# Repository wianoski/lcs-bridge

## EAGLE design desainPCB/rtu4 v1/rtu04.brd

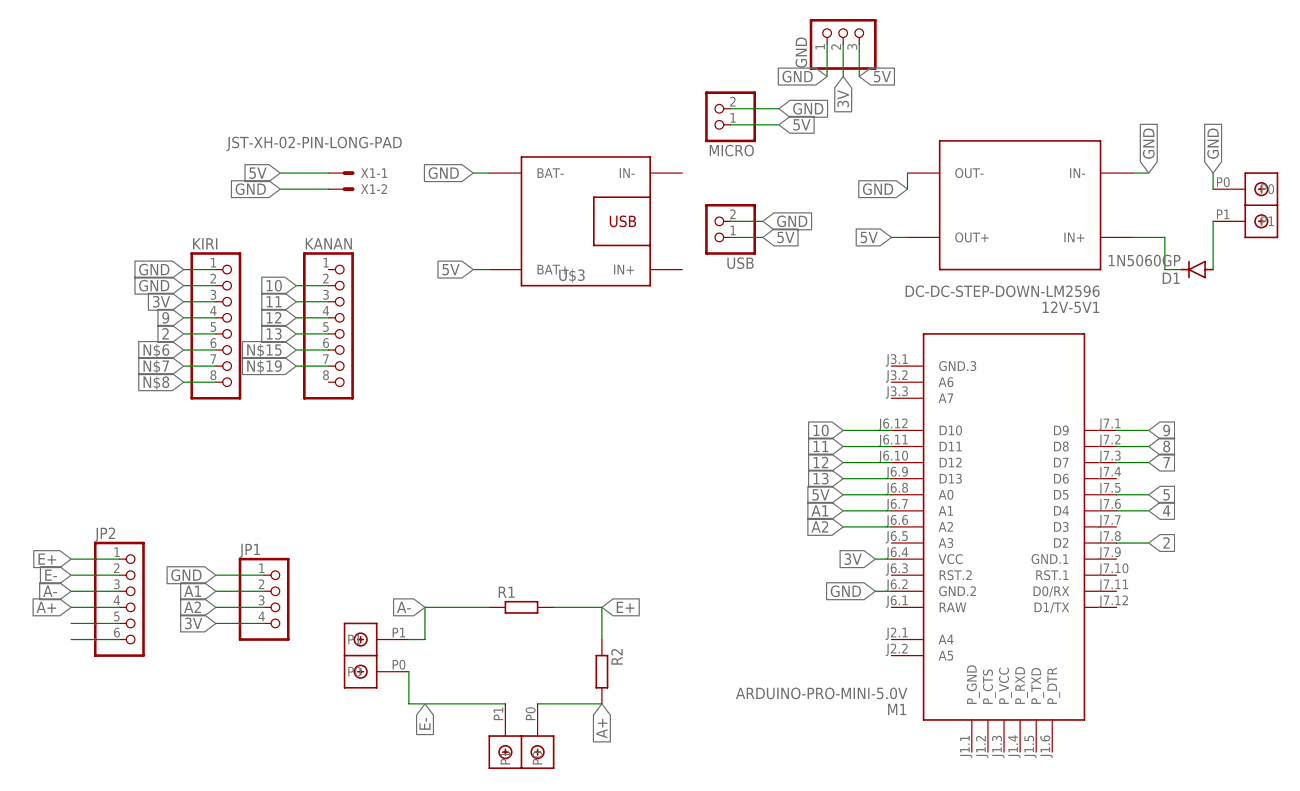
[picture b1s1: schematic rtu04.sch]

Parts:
12V-5V1: DC-DC-STEP-DOWN-LM2596
D1: 1N5060GP; DO15-12
GND: PINHD-1X3; 1X03
JP1: PINHD-1X4; 1X04
JP2: PINHD-1X6; 1X06
KANAN: PINHD-1X8; 1X08
KIRI: PINHD-1X8; 1X08
M1: ARDUINO-PRO-MINI-5.0V; ARDUINO-PRO-MINI
MICRO: PINHD-1X2; 1X02
R1, R2: R-EU_0207/10; 0207/10
U$1, U$2, U$4: DBCONN-1X2
U$3: BATTERY-CHARGER-LI-5V
USB: PINHD-1X2; 1X02
X1: JST-XH-02-PIN-LONG-PAD; JST-XH-02-PACKAGE-LONG-PAD

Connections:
2: KIRI.5, M1.J7.8 (D2)
3V: GND.2, JP1.4, KIRI.3, M1.J6.4 (VCC)
4: M1.J7.6 (D4)
5: M1.J7.5 (D5)
5V: 12V-5V1.OUT+, GND.3, M1.J6.8 (A0), MICRO.1, U$3.BAT+, USB.1, X1.1
7: M1.J7.3 (D7)
8: M1.J7.2 (D8)
9: KIRI.4, M1.J7.1 (D9)
10: KANAN.2, M1.J6.12 (D10)
11: KANAN.3, M1.J6.11 (D11)
12: KANAN.4, M1.J6.10 (D12)
13: KANAN.5, M1.J6.9 (D13)
A1: JP1.2, M1.J6.7 (A1)
A2: JP1.3, M1.J6.6 (A2)
A+: JP2.4, R2.2, U$2.P0
A-: JP2.3, R1.1, U$4.P1
E+: JP2.1, R1.2, R2.1
E-: JP2.2, U$2.P1, U$4.P0
GND: 12V-5V1.IN-, 12V-5V1.OUT-, GND.1, JP1.1, KIRI.1, KIRI.2, M1.J6.2 (GND.2), MICRO.2, U$1.P0, U$3.BAT-, USB.2, X1.2
GND.1: M1.J7.9 (GND.1)
unnamed: 12V-5V1.IN+, D1.C
unnamed: D1.A, U$1.P1
RAW: M1.J6.1 (RAW)

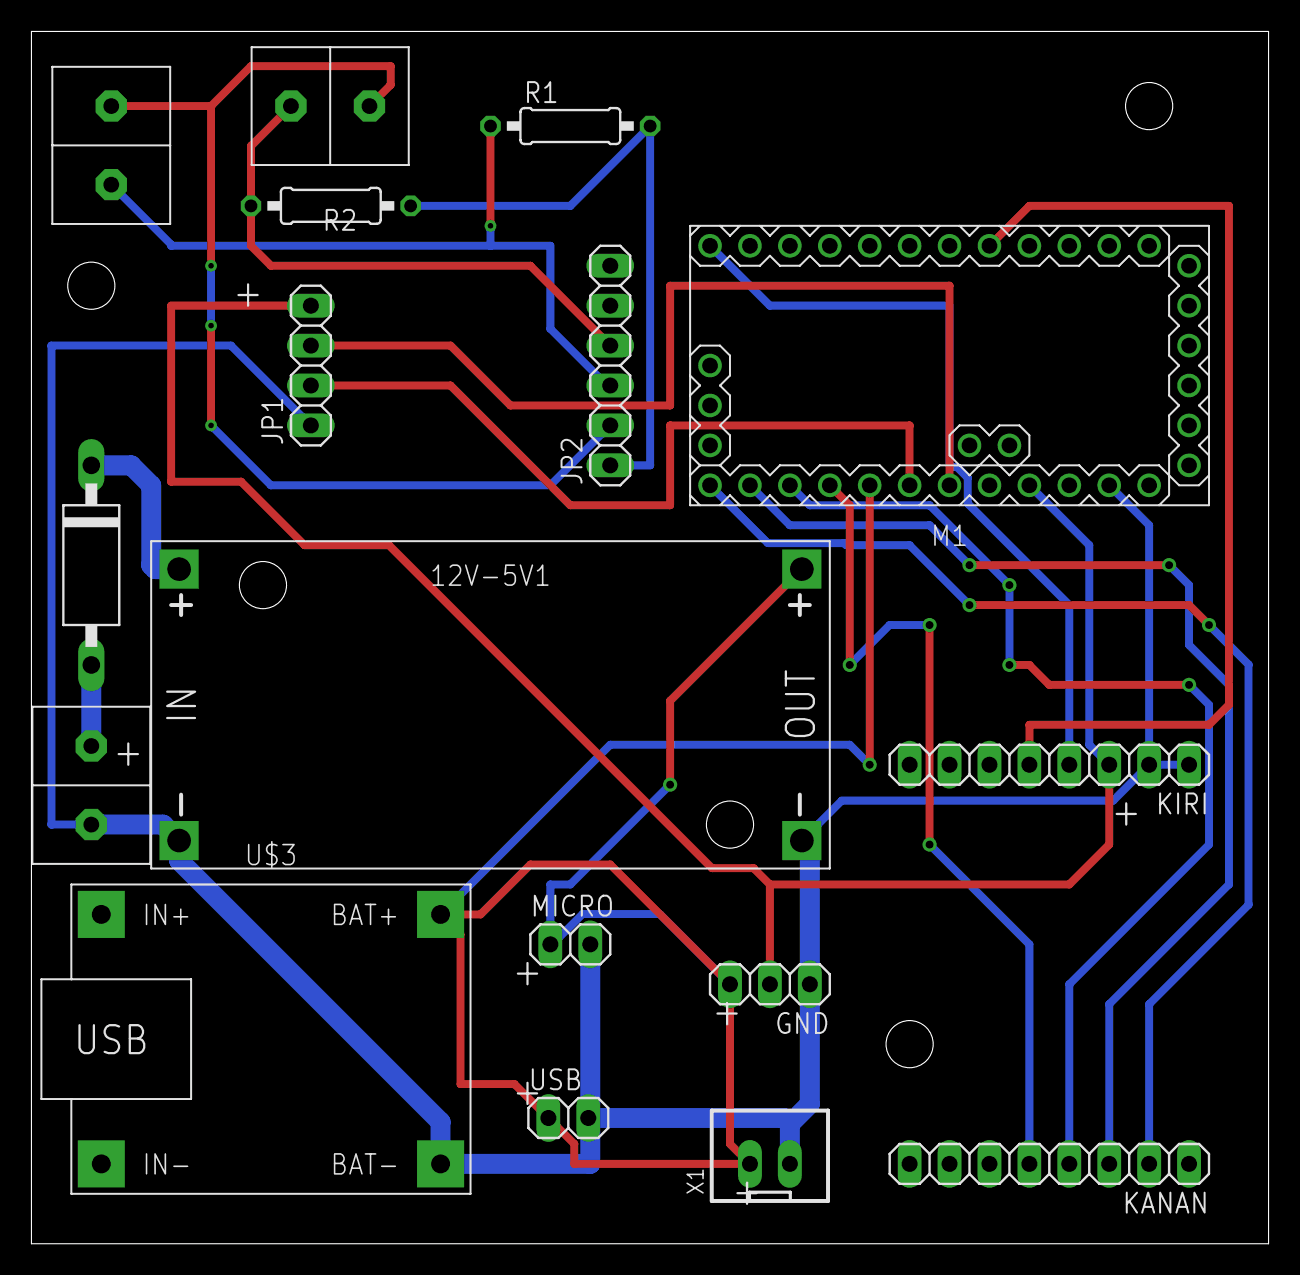
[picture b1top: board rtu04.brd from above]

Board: 2 copper layers, 78.7 x 77.1 mm, 17 parts (0 on the bottom side), 17 nets.

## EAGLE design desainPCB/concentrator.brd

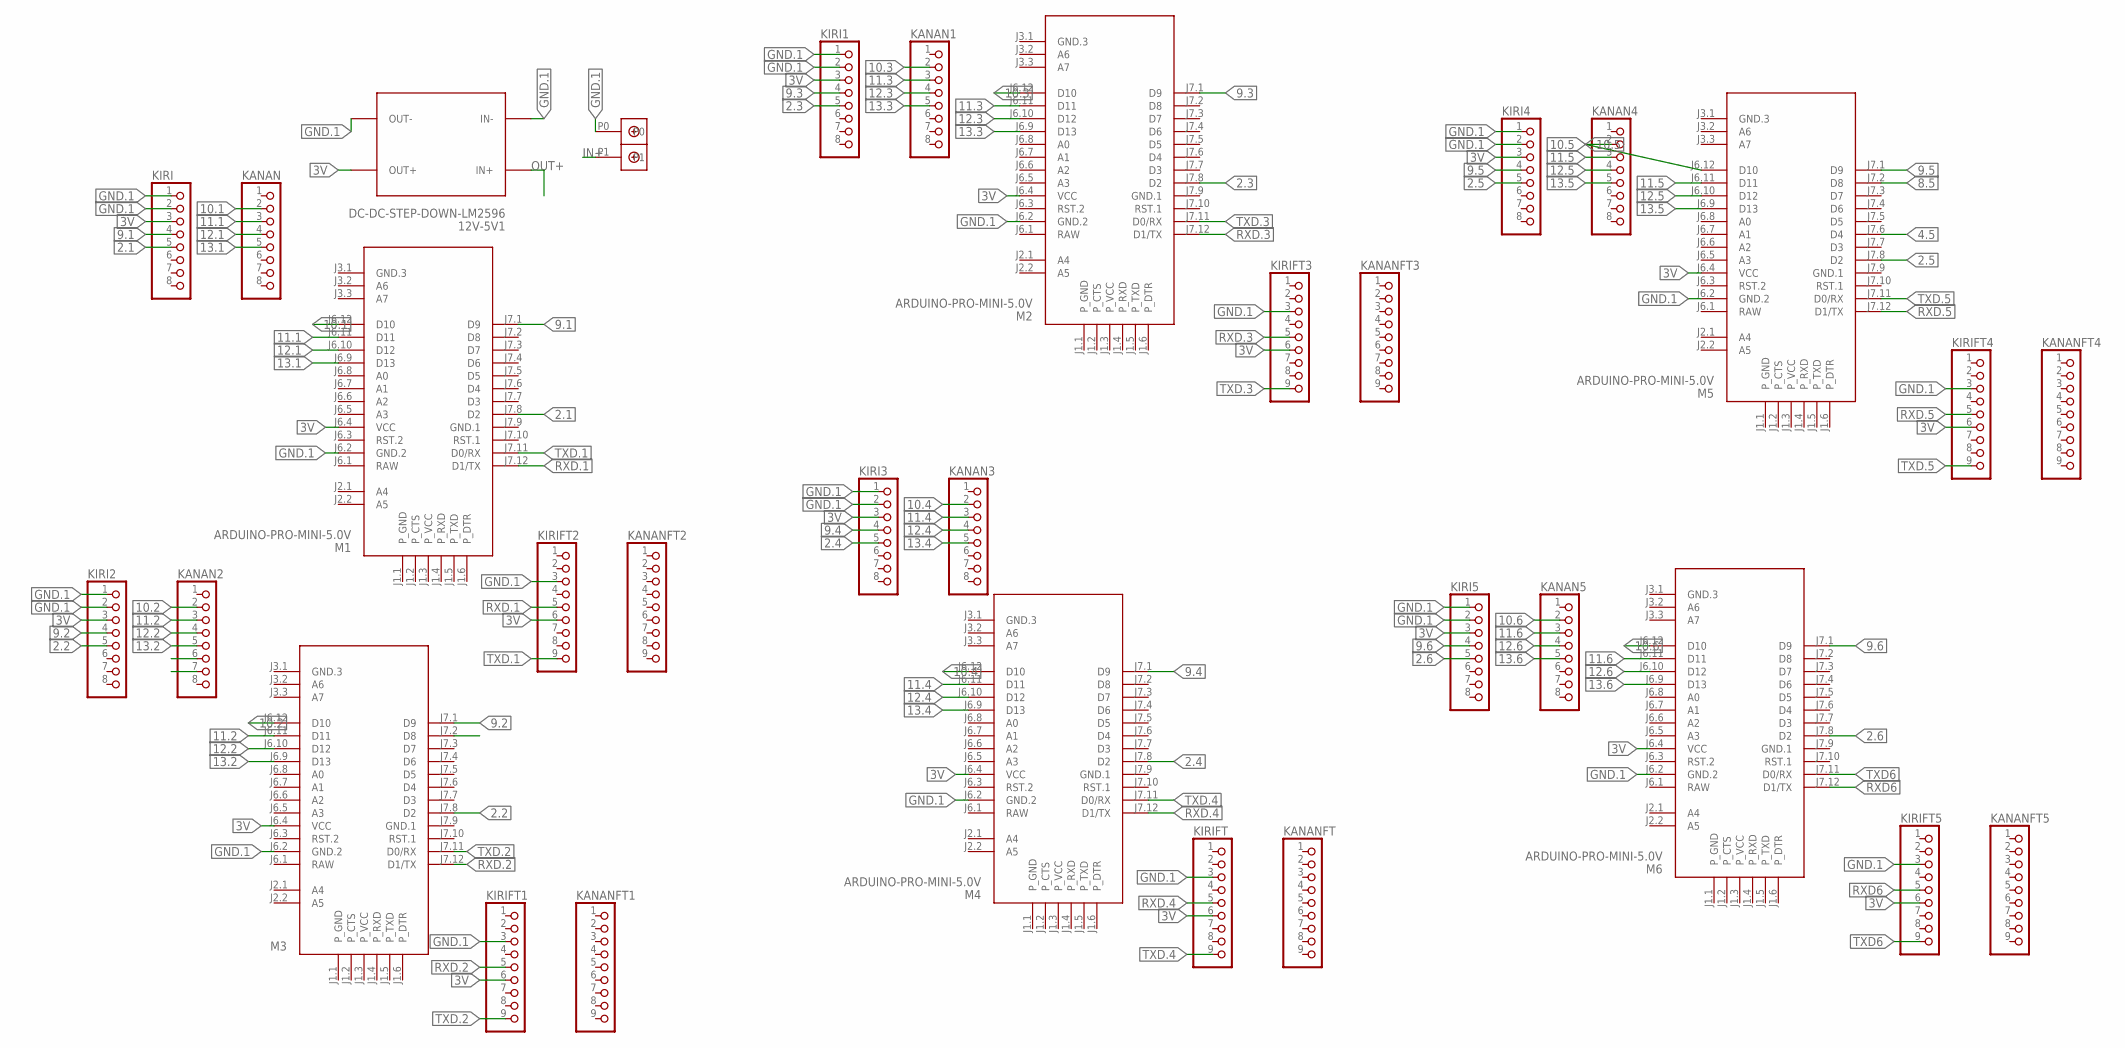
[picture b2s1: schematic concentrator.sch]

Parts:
12V-5V1: DC-DC-STEP-DOWN-LM2596
KANAN, KANAN1, KANAN2, KANAN3, KANAN4, KANAN5: PINHD-1X8; 1X08
KANANFT, KANANFT1, KANANFT2, KANANFT3, KANANFT4, KANANFT5: PINHD-1X9; 1X09
KIRI, KIRI1, KIRI2, KIRI3, KIRI4, KIRI5: PINHD-1X8; 1X08
KIRIFT, KIRIFT1, KIRIFT2, KIRIFT3, KIRIFT4, KIRIFT5: PINHD-1X9; 1X09
M1, M2, M3, M4, M5, M6: ARDUINO-PRO-MINI-5.0V; ARDUINO-PRO-MINI
U$1: DBCONN-1X2

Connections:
1: M1.J6.1 (RAW), M2.J6.1 (RAW), M3.J6.1 (RAW), M4.J6.1 (RAW), M5.J6.1 (RAW), M6.J6.1 (RAW)
2.1: KIRI.5, M1.J7.8 (D2)
2.2: KIRI2.5, M3.J7.8 (D2)
2.3: KIRI1.5, M2.J7.8 (D2)
2.4: KIRI3.5, M4.J7.8 (D2)
2.5: KIRI4.5, M5.J7.8 (D2)
2.6: KIRI5.5, M6.J7.8 (D2)
3V: 12V-5V1.OUT+, KIRI.3, KIRI1.3, KIRI2.3, KIRI3.3, KIRI4.3, KIRI5.3, KIRIFT.6, KIRIFT1.6, KIRIFT2.6, KIRIFT3.6, KIRIFT4.6, KIRIFT5.6, M1.J6.4 (VCC), M2.J6.4 (VCC), M3.J6.4 (VCC), M4.J6.4 (VCC), M5.J6.4 (VCC), M6.J6.4 (VCC)
4.5: M5.J7.6 (D4)
8: M3.J7.2 (D8)
8.5: M5.J7.2 (D8)
9.1: KIRI.4, M1.J7.1 (D9)
9.2: KIRI2.4, M3.J7.1 (D9)
9.3: KIRI1.4, M2.J7.1 (D9)
9.4: KIRI3.4, M4.J7.1 (D9)
9.5: KIRI4.4, M5.J7.1 (D9)
9.6: KIRI5.4, M6.J7.1 (D9)
10.1: KANAN.2, M1.J6.12 (D10)
10.2: KANAN2.2, M3.J6.12 (D10)
10.3: KANAN1.2, M2.J6.12 (D10)
10.4: KANAN3.2, M4.J6.12 (D10)
10.5: KANAN4.2, M5.J6.12 (D10)
10.6: KANAN5.2, M6.J6.12 (D10)
11.1: KANAN.3, M1.J6.11 (D11)
11.2: KANAN2.3, M3.J6.11 (D11)
11.3: KANAN1.3, M2.J6.11 (D11)
11.4: KANAN3.3, M4.J6.11 (D11)
11.5: KANAN4.3, M5.J6.11 (D11)
11.6: KANAN5.3, M6.J6.11 (D11)
12.1: KANAN.4, M1.J6.10 (D12)
12.2: KANAN2.4, M3.J6.10 (D12)
12.3: KANAN1.4, M2.J6.10 (D12)
12.4: KANAN3.4, M4.J6.10 (D12)
12.5: KANAN4.4, M5.J6.10 (D12)
12.6: KANAN5.4, M6.J6.10 (D12)
13.1: KANAN.5, M1.J6.9 (D13)
13.2: KANAN2.5, M3.J6.9 (D13)
13.3: KANAN1.5, M2.J6.9 (D13)
13.4: KANAN3.5, M4.J6.9 (D13)
13.5: KANAN4.5, M5.J6.9 (D13)
13.6: KANAN5.5, M6.J6.9 (D13)
GND.1: 12V-5V1.IN-, 12V-5V1.OUT-, KIRI.1, KIRI.2, KIRI1.1, KIRI1.2, KIRI2.1, KIRI2.2, KIRI3.1, KIRI3.2, KIRI4.1, KIRI4.2, KIRI5.1, KIRI5.2, KIRIFT.3, KIRIFT1.3, KIRIFT2.3, KIRIFT3.3, KIRIFT4.3, KIRIFT5.3, M1.J6.2 (GND.2), M1.J7.9 (GND.1), M2.J6.2 (GND.2), M2.J7.9 (GND.1), M3.J6.2 (GND.2), M3.J7.9 (GND.1), M4.J6.2 (GND.2), M4.J7.9 (GND.1), M5.J6.2 (GND.2), M5.J7.9 (GND.1), M6.J6.2 (GND.2), M6.J7.9 (GND.1), U$1.P0
IN+: U$1.P1
OUT+: 12V-5V1.IN+
RXD6: KIRIFT5.5, M6.J7.12 (D1/TX)
RXD.1: KIRIFT2.5, M1.J7.12 (D1/TX)
RXD.2: KIRIFT1.5, M3.J7.12 (D1/TX)
RXD.3: KIRIFT3.5, M2.J7.12 (D1/TX)
RXD.4: KIRIFT.5, M4.J7.12 (D1/TX)
RXD.5: KIRIFT4.5, M5.J7.12 (D1/TX)
TXD6: KIRIFT5.9, M6.J7.11 (D0/RX)
TXD.1: KIRIFT2.9, M1.J7.11 (D0/RX)
TXD.2: KIRIFT1.9, M3.J7.11 (D0/RX)
TXD.3: KIRIFT3.9, M2.J7.11 (D0/RX)
TXD.4: KIRIFT.9, M4.J7.11 (D0/RX)
TXD.5: KIRIFT4.9, M5.J7.11 (D0/RX)

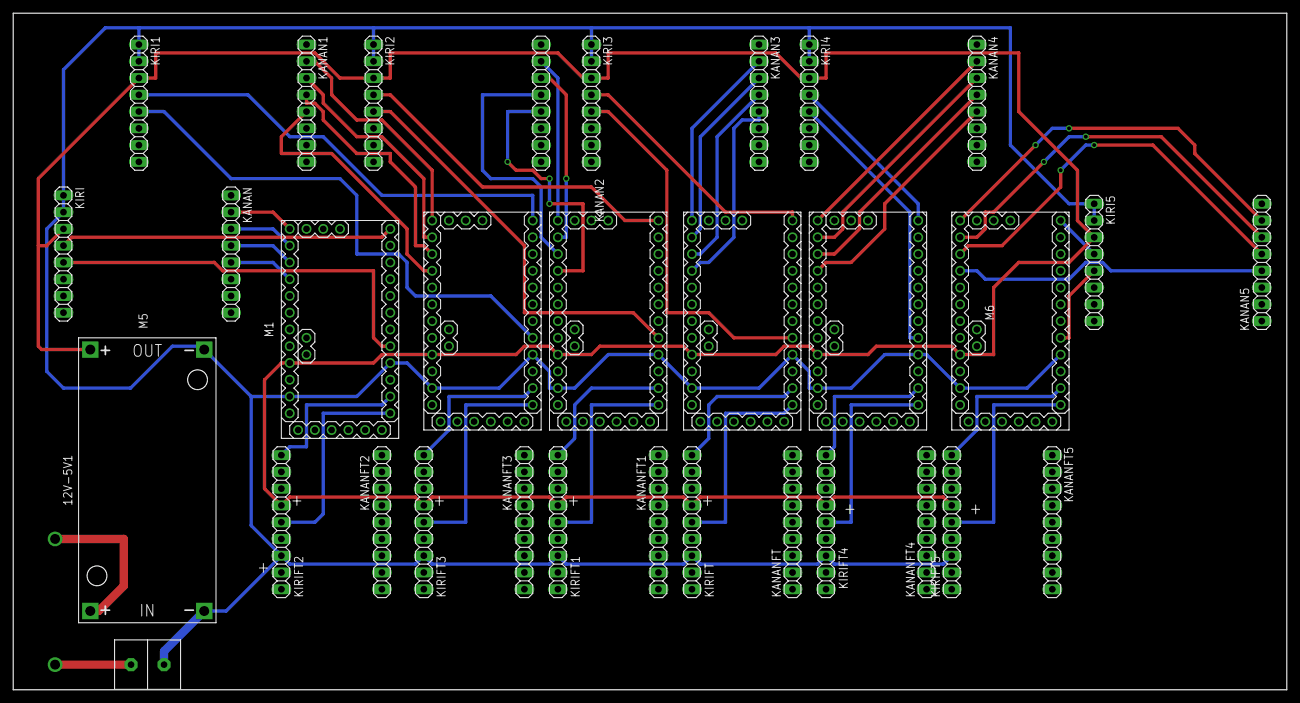
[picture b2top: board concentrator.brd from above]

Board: 2 copper layers, 193.0 x 102.5 mm, 32 parts (0 on the bottom side), 51 nets.

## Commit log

2020-06-25 fix binary
2020-06-25 ubah biner jadi hex
2020-06-26 mpu stuff
2020-06-27 another hex
2020-06-29 hardware calibration
2020-06-30 comm
2020-07-01 hex lagi hex lagi
2020-07-02 almost there
2020-07-04 what is this ?
2020-07-07 fix header
2020-07-07 added vars
2020-07-09 fix rtu01, 02-04 mengikuti
2020-07-10 fixed again fuck
2020-07-15 final bisa
2020-07-16 backend
2020-07-20 web side
2020-07-22 fixed 01
2020-07-23 fixed payload for graph
2020-07-25 idk what is this
2020-07-28 fix freq
2020-07-29 fixed all
2020-07-30 added webserv
2020-08-04 cam session
2020-08-05 rtu03
2020-08-07 prep
2020-08-10 fixed for presentation
2020-08-14 firmware
2020-08-19 before holiday
2020-08-24 cam trigger
2020-08-26 trigger done
2020-09-01 new sensor suhu
2020-09-08 finally back with fuse n lock
2020-09-11 preparing for the new vessel
2020-09-12 update sabtu
2020-09-12 update id
2020-09-14 update senin
2020-09-16 update rabu
2020-09-17 update kamis, perbaikan header gateway
2020-09-17 gateway 05 fixed
2020-09-22 added Z
2020-09-22 salah nama
2020-09-24 persiapan demo jumat
2020-09-28 desain baru pcb
2020-10-01 compress image
2020-10-02 fix gyro2
2020-10-05 preparing strain calib
2020-10-06 fix 2.1 gyro
2020-10-07 calib mass
2020-10-13 read for caliob
2020-10-16 change at strain board, gyro and more!
2020-10-19 fix calib for strain 2.0
2020-10-20 aaa{
2020-10-21 fix callib anjing
2020-10-27 graf
2020-10-30 jumat tgl 30
2020-11-02 final day
2020-11-06 capek gw
2020-11-09 update untuk rtu acc, snapshot zoom
2020-11-10 test range and start to migrate local storage
2020-11-11 record local done
2020-11-12 tilt ok
2020-11-12 just in case, deg/s
2020-11-13 happy weekend !
2020-11-16 senin
2020-11-23 hari h
2020-12-02 fix strain n gyro
2020-12-03 strain again
2020-12-07 post processing data
2020-12-08 preparing
2020-12-08 preparinggg
2020-12-08 minggu ini
2020-12-11 filter strain
2020-12-15 selasa
2020-12-16 rabu
2021-01-07 kamis
2021-01-22 jumat
2021-01-29 jujmat
2021-04-11 update for 2byte separation

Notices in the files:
parts and their libraries:
diy-modules: Released under the Creative Commons Attribution 4.0 International License: http://creativecommons.org/licenses/by/4.0
